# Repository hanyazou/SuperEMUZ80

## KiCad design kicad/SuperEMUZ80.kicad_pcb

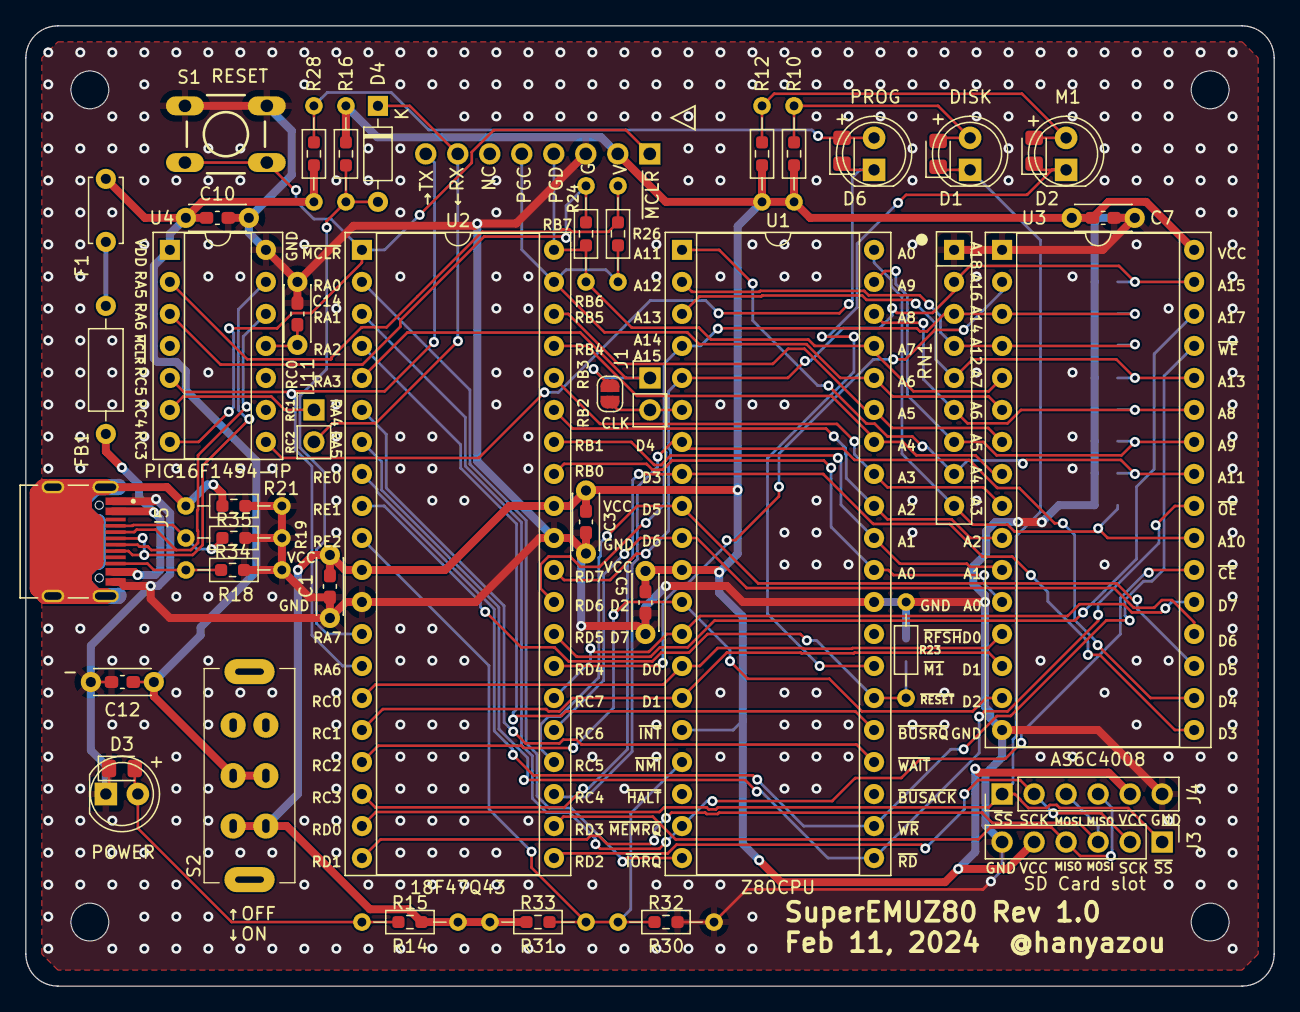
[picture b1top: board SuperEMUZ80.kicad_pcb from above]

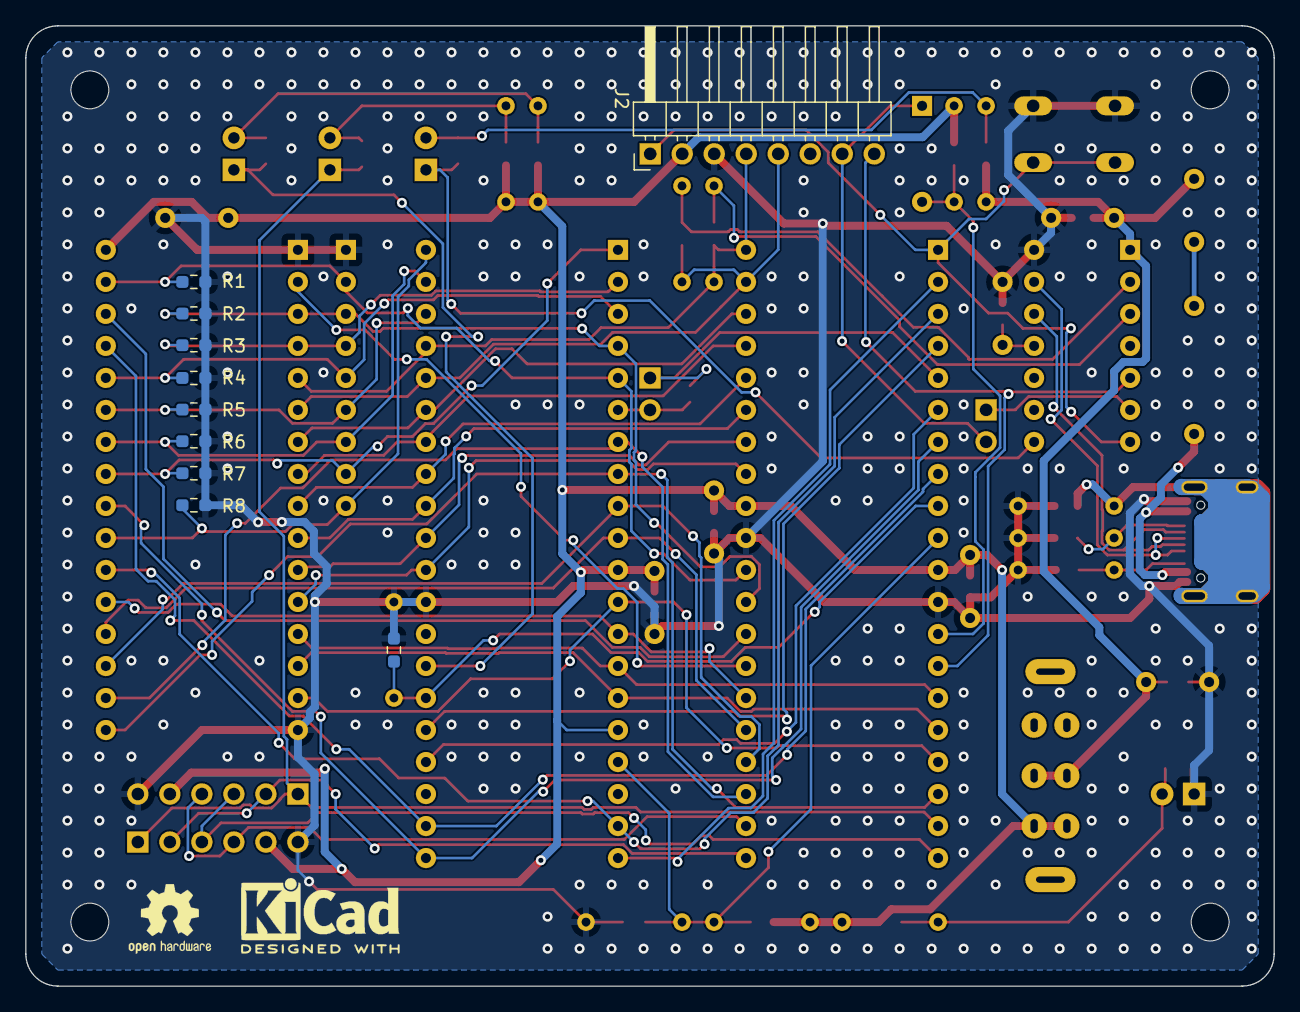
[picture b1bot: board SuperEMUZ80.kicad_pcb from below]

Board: 2 copper layers, 99.1 x 76.2 mm, 73 parts (10 on the bottom side), 64 nets.

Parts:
C1, C3, C5, C7, C10: 0.1uF; C_Disc_D4.3mm_W1.9mm_P5.00mm
C2, C4, C6, C8, C9: 0.1uF; C_0603_1608Metric_Pad1.08x0.95mm_HandSolder
C11: 1uF; C_0603_1608Metric_Pad1.08x0.95mm_HandSolder
C12: 1uF; C_Disc_D4.3mm_W1.9mm_P5.00mm
C13: 0.47uF; C_0603_1608Metric_Pad1.08x0.95mm_HandSolder
C14: 0.47uF; C_Disc_D4.3mm_W1.9mm_P5.00mm
D1, D2, D3, D6: LED; LED_D5.0mm
D4: 1N4148; D_DO-35_SOD27_P7.62mm_Horizontal
D5, D7, D8, D9: LED; LED_0805_2012Metric_Pad1.15x1.40mm_HandSolder
F1: Polyfuse; C_Disc_D5.0mm_W2.5mm_P5.00mm
FB1: FerriteBead_Small; R_Axial_DIN0207_L6.3mm_D2.5mm_P10.16mm_Horizontal
J1, J11: Conn_02x01; PinHeader_1x02_P2.54mm_Vertical
J2: Conn_01x08_Pin; PinHeader_1x08_P2.54mm_Horizontal
J3, J4: SD Card slot; PinHeader_1x06_P2.54mm_Vertical
J5: 5077CR-16SMC2-BK-TR; NELTRON_5077CR-16SMC2-BK-TR
JP1: Jumper_2_Open; SolderJumper-2_P1.3mm_Open_RoundedPad1.0x1.5mm
R1, R2, R3, R4, R5, R6, R7, R8, R17, R22, R33: 10K; R_0603_1608Metric_Pad0.98x0.95mm_HandSolder
R10, R12, R14, R28: 100; R_Axial_DIN0204_L3.6mm_D1.6mm_P7.62mm_Horizontal
R11, R13, R15, R29: 100; R_0603_1608Metric_Pad0.98x0.95mm_HandSolder
R16, R23, R31: 10K; R_Axial_DIN0204_L3.6mm_D1.6mm_P7.62mm_Horizontal
R18, R19: 5k1; R_Axial_DIN0204_L3.6mm_D1.6mm_P7.62mm_Horizontal
R20: 1M; R_0603_1608Metric_Pad0.98x0.95mm_HandSolder
R21: 1M; R_Axial_DIN0204_L3.6mm_D1.6mm_P7.62mm_Horizontal
R24, R26: 470; R_Axial_DIN0204_L3.6mm_D1.6mm_P7.62mm_Horizontal
R25, R27: 470; R_0603_1608Metric_Pad0.98x0.95mm_HandSolder
R30: 39K; R_Axial_DIN0204_L3.6mm_D1.6mm_P7.62mm_Horizontal
R32: 39K; R_0603_1608Metric_Pad0.98x0.95mm_HandSolder
R34, R35: 5k1; R_0603_1608Metric_Pad0.98x0.95mm_HandSolder
RN1: 10K; R_Array_SIP9
S1: DTS-6
S2: POWER; SS22F06
U1: Z80CPU; DIP-40_W15.24mm_Socket
U2: 18F47Q43; DIP-40_W15.24mm_Socket
U3: AS6C4008; DIP-32_W15.24mm_Socket
U4: PIC16F1454-IP; DIP-14_W7.62mm_Socket

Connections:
A0: U1.30 (A0), U2.33 (RB0), U3.12 (A0)
A1: U1.31 (A1), U2.34 (RB1), U3.11 (A1)
A2: U1.32 (A2), U2.35 (RB2), U3.10 (A2)
A3: U1.33 (A3), U2.36 (RB3), U3.9 (A3)
A4: U1.34 (A4), U2.37 (RB4), U3.8 (A4)
A5: U1.35 (A5), U2.38 (RB5), U3.7 (A5)
A6: J2.5, R26.2, R27.2, U1.36 (A6), U2.39 (RB6/ICSPC), U3.6 (A6)
A7: J2.4, R24.2, R25.2, U1.37 (A7), U2.40 (RB7/ICSPD), U3.5 (A7)
A8: R5.1, RN1.6 (R5), U1.38 (A8), U3.27 (A8)
A9: R6.1, RN1.7 (R6), U1.39 (A9), U3.26 (A9)
A10: R8.1, RN1.9 (R8), U1.40 (A10), U3.23 (A10)
A11: R7.1, RN1.8 (R7), U1.1 (A11), U3.25 (A11)
A12: R3.1, RN1.4 (R3), U1.2 (A12), U3.4 (A12)
A13: R4.1, RN1.5 (R4), U1.3 (A13), U3.28 (A13)
A14: R2.1, RN1.3 (R2), U1.4 (A14), U2.29 (RD6), U3.3 (A14)
A15: R1.1, RN1.2 (R1), U1.5 (A15), U2.30 (RD7), U3.31 (A15)
A16: U2.27 (RD4), U3.2 (A16)
A17: U2.28 (RD5), U3.30 (A17)
CLK: J1.2, JP1.2 (B), U1.6 (~CLK)
CLK_GEN: J1.1, JP1.1 (A), U2.5 (RA3)
D0: U1.14 (D0), U2.15 (RC0), U3.13 (Q0)
D1: U1.15 (D1), U2.16 (RC1), U3.14 (Q1)
D2: U1.12 (D2), U2.17 (RC2), U3.15 (Q2)
D3: U1.8 (D3), U2.18 (RC3), U3.17 (Q3)
D4: U1.7 (D4), U2.23 (RC4), U3.18 (Q4)
D5: U1.9 (D5), U2.24 (RC5), U3.19 (Q5)
D6: U1.10 (D6), U2.25 (RC6), U3.20 (Q6)
D7: U1.13 (D7), U2.26 (RC7), U3.21 (Q7)
GND: C1.2, C2.2, C3.2, C4.2, C5.2, C6.2, C7.2, C8.2, C9.2, C10.2, C11.2, C12.2, C13.2, C14.2, D3.1 (K), D9.1 (K), J2.3, J3.6, J4.6, J5.A1_B12 (GND), J5.B1_A12 (GND), R1.2, R2.2, R3.2, R4.2, R5.2, R6.2, R7.2, R8.2, R18.2, R19.2, R20.2, R21.2, R22.2, R23.2, R30.2, R32.2, R34.2, R35.2, RN1.1 (common), S1.3, S1.4, U1.29 (GND), U2.12 (VSS), U2.31 (VSS), U3.1 (A18), U3.16 (GND), U4.14 (VSS)
LED: D5.1 (K), D6.1 (K), U4.8 (SDO/RC2)
MISO: J3.4, J4.4, U2.22 (RD3)
MOSI: J3.3, J4.3, U2.20 (RD1)
unnamed: D1.2 (A), D7.2 (A), R10.2, R11.2
unnamed: D2.2 (A), D8.2 (A), R12.2, R13.2
unnamed: D3.2 (A), D9.2 (A), R14.2, R15.2
unnamed: D4.1 (K), J2.7, J11.2
unnamed: D5.2 (A), D6.2 (A), R28.1, R29.1
unnamed: F1.2, FB1.1
unnamed: J5.A5 (CC1), R19.1, R35.1
unnamed: J5.B5 (CC2), R18.1, R34.1
PIC_RX: D4.2 (A), R16.2, R17.2, U2.13 (RA7)
PROG_TX: J11.1, U4.6 (CK/TX/RC4)
RA4: R24.1, R25.1, U4.3 (RA4/SOSCO/T1G/SDO/CLKOUT/OSC2/CLKR)
RA5: R26.1, R27.1, U4.2 (RA5/SOSCI/T1CKI/PWM2/CLKIN/OSC1)
SCK: J3.2, J4.2, U2.21 (RD2)
SHIELD: J5.S1 (SHIELD), J5.S2 (SHIELD), J5.S3 (SHIELD), J5.S4 (SHIELD), R20.1, R21.1
TX: J2.8, U2.14 (RA6), U4.5 (PWM1/DT/RX/T0CKI/RC5)
USB_DM: J5.A7 (DN1), J5.B7 (DN2), U4.12 (RA1/D-/ICSPCLK)
USB_DP: J5.A6 (DP1), J5.B6 (DP2), U4.13 (RA0/D+/ICSPDAT)
VBUS: FB1.2, J5.A4_B9 (VBUS), J5.B4_A9 (VBUS)
VCC: C1.1, C2.1, C3.1, C4.1, C5.1, C6.1, C7.1, C8.1, J2.2, J3.5, J4.5, R10.1, R11.1, R12.1, R13.1, R14.1, R15.1, R16.1, R17.1, R31.1, R33.1, S2.1 (1A1), S2.6 (2A1), U1.11 (VCC), U1.16 (~INT), U2.11 (VDD), U2.32 (VDD), U3.32 (VCC)
VDD: C9.1, C10.1, C11.1, C12.1, F1.1, R28.2, R29.2, S2.2 (1A2), S2.5 (2A2), U4.1 (VDD)
VUSB3V3: C13.1, C14.1, U4.11 (Vusb3v3)
~BUSRQ: U1.25 (~BUSRQ), U2.4 (RA2)
~IORQ: U1.20 (~IORQ), U2.2 (RA0)
~M1: D2.1 (K), D8.1 (K), U1.27 (~M1)
~MCLR: J2.1, S1.1, S1.2, U2.1 (~MCLR/RE3), U4.7 (CLKR/~SS/PWM2/RC3)
~MREQ: U1.19 (~MREQ), U2.3 (RA1), U3.22 (~CE)
~NMI: R30.1, R31.2, R32.1, R33.2, U1.17 (~NMI), U2.10 (RE2)
~RD: U1.21 (~RD), U2.7 (RA5), U3.24 (~OE)
~RESET: R22.1, R23.1, U1.26 (~RESET), U2.9 (RE1)
~SS: D1.1 (K), D7.1 (K), J3.1, J4.1, U2.19 (RD0)
~WAIT: U1.24 (~WAIT), U2.6 (RA4)
~WR: U1.22 (~WR), U2.8 (RE0), U3.29 (~WE)

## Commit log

2024-02-04 Add SuperEMUZ80 version 0.9
2024-02-11 Add SuperEMUZ80 version 1.0
